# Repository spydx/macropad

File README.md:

# Macro Pad

This is a small macropad inspired by the Figma Pad from Worklouder Figma Creator.

## v1.1

The first version, I did some mistakes and are not entirely happy with it. I managed to wire the OLED wrong, and are not happy with the placement of the microcontroller.

v1.1 contains fixes for:

- OLED Wiring (mixed up SDA & SCL signal)
- Flipped Diode (only on the board)

If you wanna build it, you can follow the instructions in the [README](v1.1/README.md)

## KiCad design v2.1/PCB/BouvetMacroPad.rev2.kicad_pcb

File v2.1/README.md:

# Macropad v1.1

My first attempt on build a 14 key macropad with two rotary encoders.

Read everything first, this is a very thin guide of what you need, the rest you are on your own.

## What you need

| Count | Component | Link |
| ---- | --- | --- |
|  1 | PCB | JLCPCB or any other |
|  1 | WaveShare RP2040-Zero USB-C| [WaveShare](https://www.waveshare.com/rp2040-zero.htm?sku=20335) |
| 14 | 1N4148 Diodes | [Mouser](https://no.mouser.com/ProductDetail/onsemi-Fairchild/1N4148?qs=i4Fj9T%2FoRm8RMUhj5DeFQg%3D%3D) |
| 12 | Kailh Choc V2 Low Profiles Keys | [Max Gamming](https://www.maxgaming.no/no/switchar/choc-v2-low-profile-brown) |
|  2 | Rotary Encoderss PEC12R-2120F-S0012 | [Mouser](https://no.mouser.com/ProductDetail/Bourns/PEC12R-2120F-S0012?qs=Zq5ylnUbLm4y5zPMmL%252Bc3g%3D%3D) |
|  1 | OLED 128x32 SSD1306 I2C | [Amazon](https://www.amazon.com/128x32-SSD1306-Consumption-Display-Arduino/dp/B07PDFCVXL) |

Notes.. if you buy other parts than these they might not be compatible, inspect the schematics for details if the components will fit.

You will need knobs for the encoders and keycaps, see 3D print section.

## PCB

The [PCB](PCB/production/BouvetMacroPad-Rev2.1.zip) can be used to produce the new Rev 2.1 version of the macropad.

You can get PCBs printed from PCBWay or any other.

## Soldering

Recommended soldering order

- Diodes
- Microcontroller
- Switches
- Rotary Encoders
- OLED

## 3D printed Parts

### Keycaps and Knobs

Keycaps are not mentioned here, but you will need Low Profile Keycaps that fit the Kailh Choc V2.
There are many available to be 3D printed. E.g. the following will fit: [Keycaps](https://makerworld.com/en/models/1152559-choc-v2-ultra-thin-keycaps#profileId-1156967)

Rotary encoder knobs are also needed e.g. [these](https://makerworld.com/en/models/154058-grippy-encoder-knob?from=search#profileId-169689)

### Case

There is a small case, designed by Vilde Holtet, in the [CAD](CAD) folder.

There is a STEP file of the PCB that you can use to aid the design a new case in e.g. FreeCAD.

No special setting, when printing

## QMK Firmware

This keyboard uses QMK, until the my PR has been accepted, you need to follow these special steps.

You need to download MY fork of the repository, and checkout the custom branch `custom-keyboards`.
This contains the handwired keyboard config for the macropad.

```shell
git clone https://github.com/spydx/qmk_firmware
cd qmk_firmware
git checkout bouvetv2

# Ensure that this folder is the QMK homedir
qmk config user.qmk_home=<pwd of your folder> 
qmk config user.keyboard=handwired/bouvet/macropad/v2
qmk config user.keymap=default
```

Once this is you can compile and flash the macropad.

```shell
qmk compile

# While connecting the macro pad, press and hold the top LEFT button until the macropad is detected
qmk flash 
```

Ready to use

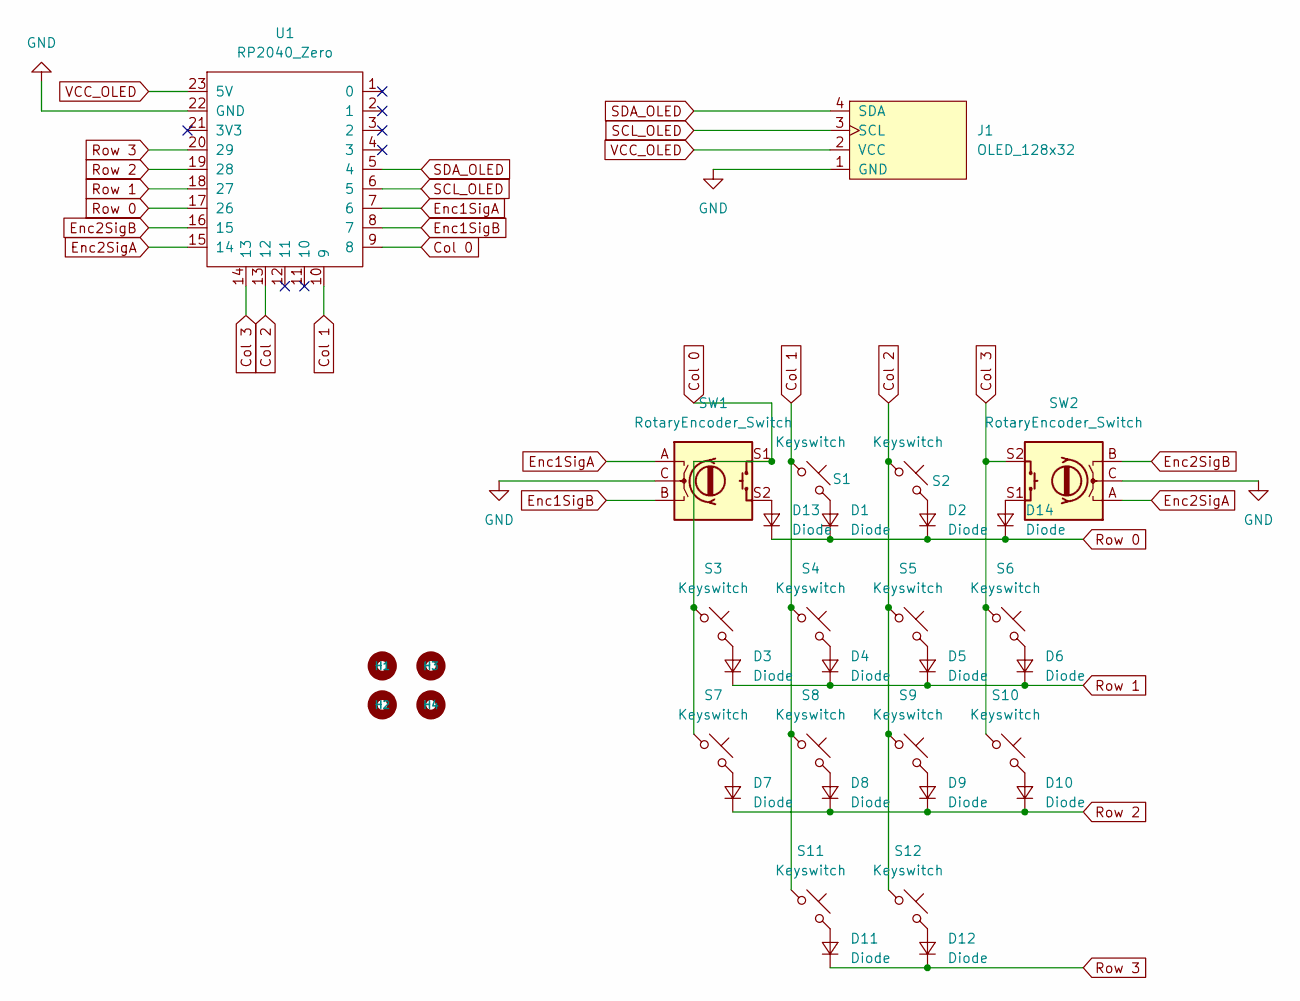
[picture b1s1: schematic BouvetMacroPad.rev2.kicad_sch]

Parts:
D1, D2, D3, D4, D5, D6, D7, D8, D9, D10, D11, D12, D13, D14: Diode; Diode_DO-35
H1, H2, H3, H4: MountingHole_5mm
J1: OLED_128x32
S1, S2, S3, S4, S5, S6, S7, S8, S9, S10, S11, S12: Keyswitch; Choc_V2_1.00u
SW1, SW2: RotaryEncoder_Switch; RotaryEncoder_Alps_EC11E-Switch_Vertical_H20mm_MountingHoles
U1: RP2040_Zero

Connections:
Col 0: S3.1, S7.1, SW1.S1, U1.9 (8)
Col 1: S1.1, S4.1, S8.1, S11.1, U1.10 (9)
Col 2: S2.1, S5.1, S9.1, S12.1, U1.13 (12)
Col 3: S6.1, S10.1, SW2.S2, U1.14 (13)
Enc1SigA: SW1.A, U1.7 (6)
Enc1SigB: SW1.B, U1.8 (7)
Enc2SigA: SW2.A, U1.15 (14)
Enc2SigB: SW2.B, U1.16 (15)
GND: J1.1 (GND), SW1.C, SW2.C, U1.22 (GND)
unnamed: D1.2 (A), S1.2
unnamed: D2.2 (A), S2.2
unnamed: D3.2 (A), S3.2
unnamed: D4.2 (A), S4.2
unnamed: D5.2 (A), S5.2
unnamed: D6.2 (A), S6.2
unnamed: D7.2 (A), S7.2
unnamed: D8.2 (A), S8.2
unnamed: D9.2 (A), S9.2
unnamed: D10.2 (A), S10.2
unnamed: D11.2 (A), S11.2
unnamed: D12.2 (A), S12.2
unnamed: D13.2 (A), SW1.S2
unnamed: D14.2 (A), SW2.S1
Row 0: D1.1 (K), D2.1 (K), D13.1 (K), D14.1 (K), U1.17 (26)
Row 1: D3.1 (K), D4.1 (K), D5.1 (K), D6.1 (K), U1.18 (27)
Row 2: D7.1 (K), D8.1 (K), D9.1 (K), D10.1 (K), U1.19 (28)
Row 3: D11.1 (K), D12.1 (K), U1.20 (29)
SCL_OLED: J1.3 (SCL), U1.6 (5)
SDA_OLED: J1.4 (SDA), U1.5 (4)
VCC_OLED: J1.2 (VCC), U1.23 (5V)

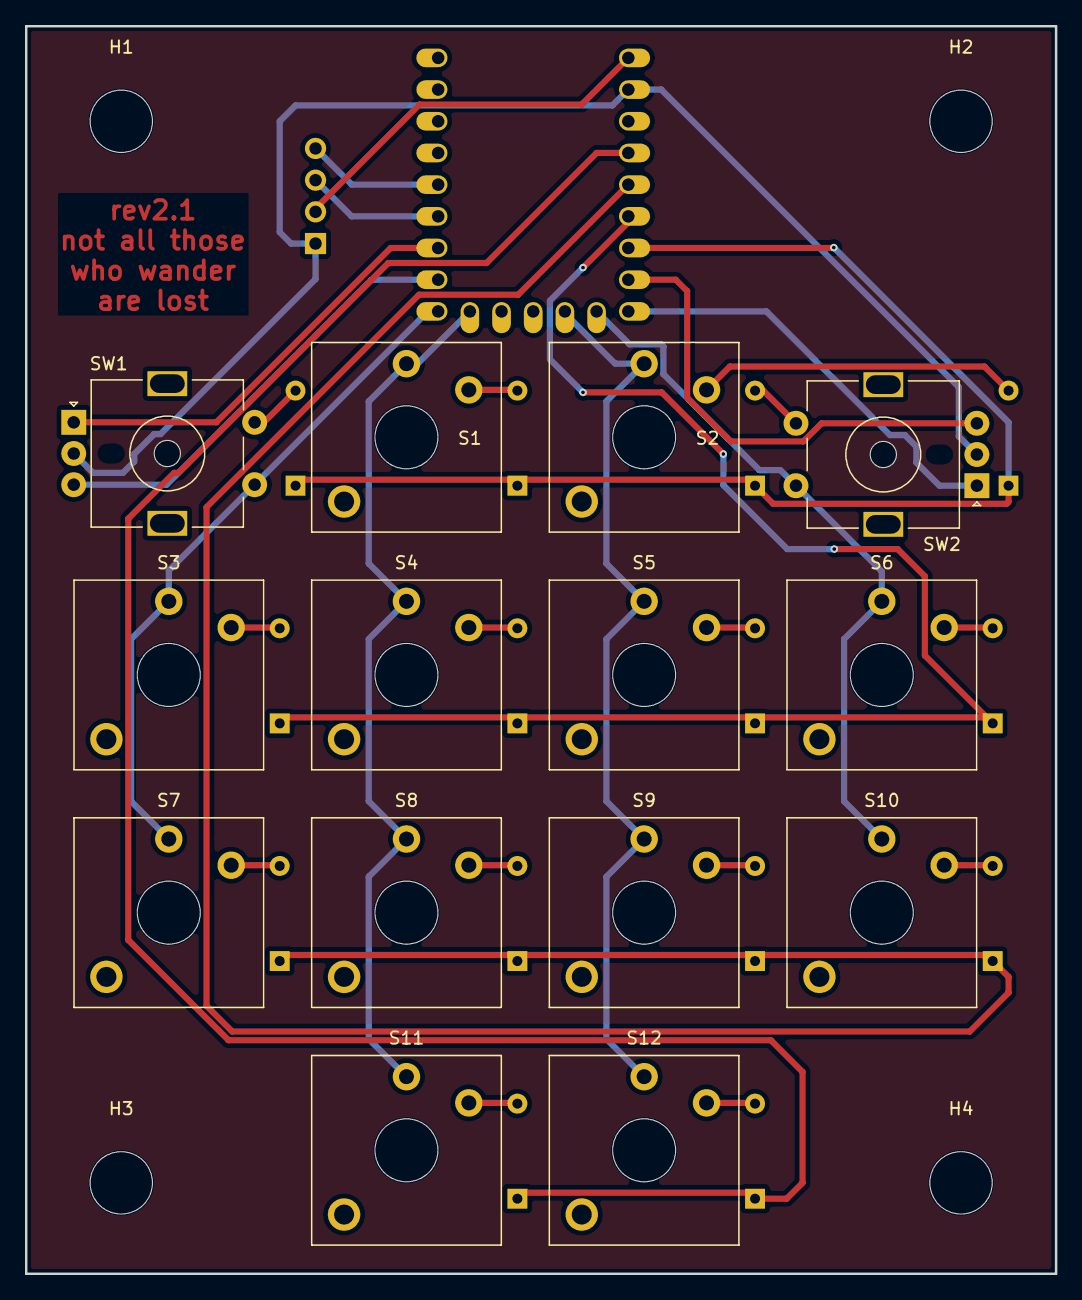
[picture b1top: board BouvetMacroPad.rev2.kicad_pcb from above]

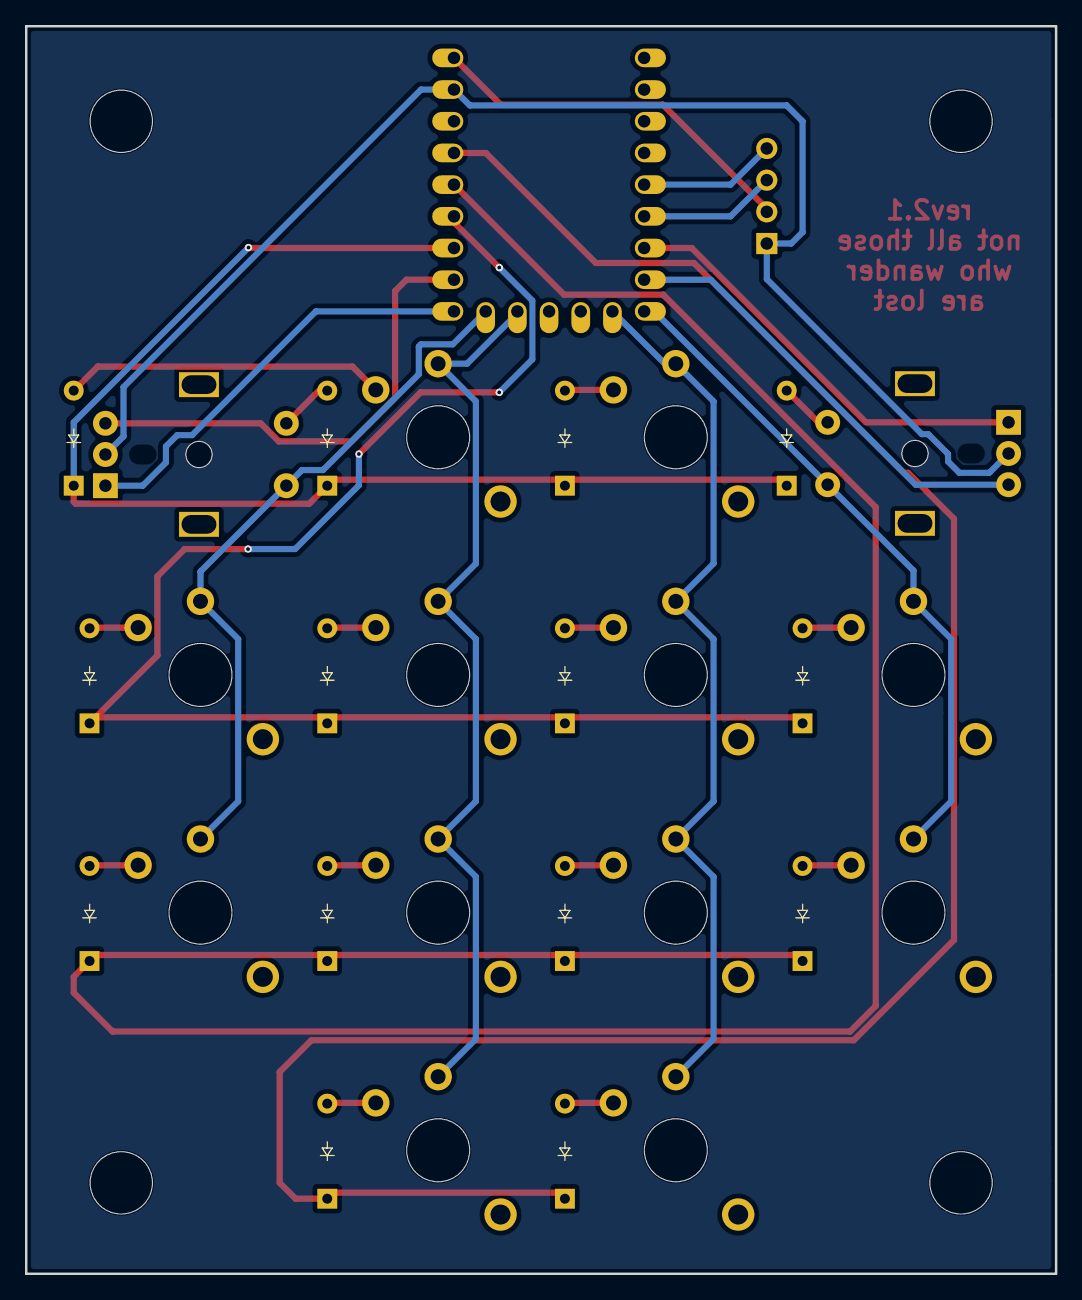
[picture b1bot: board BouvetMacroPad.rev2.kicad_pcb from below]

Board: 2 copper layers, 82.5 x 100.0 mm, 34 parts (15 on the bottom side), 30 nets.

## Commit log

2025-12-07 Rev 1.1
2026-04-15 MacroPad v2.1
2026-04-15 fix link
